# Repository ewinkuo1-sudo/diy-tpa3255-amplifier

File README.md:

# TPA3255 DIY 立體聲後級

使用 TI TPA3255 自畫電路與 PCB，搭配材料選用、3D 機構與量測，完成一台練習機／備用後級，記錄 AI 協作過程供課堂展示。

## 先看成品怎麼用

**Z10 送出音樂 → 這台後級放大 → 左右喇叭發聲。** 音量由 Z10 調整；後級機內自帶電源，機背只接一條市電電源線，另外可接 Trigger 跟隨前級開機／待機。

[白話說明與放大圖](docs/使用方式圖解.md)。這是功能與使用方式示意，外觀、內部位置及尺寸尚未定案；目前尚無實機。

## 目前進度

V0.3 已加入 **XLR 平衡輸入並保留 RCA**，搭配濾波後回授（PFFB）、四顆 Coilcraft MA5172-AE，以及隔離 Trigger、自動啟停與 48V 功率電源開關。原八頁的全部元件已按訊號路徑重新排列成 **一張連續接線的完整電路圖**，可由輸入一路看到放大、喇叭、四路回授及啟停控制；元件與電氣連接維持原版。已開始 PCB 零件配置；以 2×50W / 8Ω 為第一階段目標，尚無完成的板子或實測。

XLR 使用 INA2137 差動接收器，依 Z10 的 XLR／RCA 電平匹配音量。第一版由左右聲道跳線選擇輸入，切換前先進入待機。

整機已改為 **機內電源、機背一條市電線**：規劃單一 IEC 入口，機內分別供應 48V 主電源與 12V 待機電源。Trigger 關機只停止功率級供電，兩組 AC/DC 與 12V 支路仍有電。電源模組已有候選，交流保護、12V 入口保護、配線及熱驗證尚待完成；Z10 Trigger 的電壓、極性與帶載能力仍需實測。

## PCB 第一版配置

**[看 PCB 配置與中文說明](electrical/pcb-draft/README.md)** · [檢查結果](electrical/pcb-draft/validation.md)

已放入 180 個元件與 4 個固定孔，暫抓 22×16 公分，尺寸與料件仍需調整。**尚未走線，不能送廠製作。** 先補電源保護、定料與散熱，再細調位置和走線。

## 電路圖：輸入、放大、回授與控制接成一張大圖

**[開啟／下載單頁 PDF](electrical/v03/preview/tpa3255-v03-overview.pdf)** · [放大 SVG](electrical/v03/preview/tpa3255-v03-overview.svg) · [看圖說明](electrical/v03/README.md) · [合併檢查](electrical/v03/overview-validation.md)

總圖採 **A0 橫式單頁**，180 個元件重新編排；音訊由左往右，四路 PFFB 實際接線繞回輸入，下方整合供電與啟停控制。483 個腳位、120 個網路與原版一致，另以移除標籤的接線表確認主要路徑確實連通。PDF／SVG 可放大看數值。建議直接把單頁 PDF 傳給教授，螢幕閱讀時放大；列印以 A0 原尺寸為佳，縮到 A4 文字會太小。供電、偏壓與部分狀態線使用同名標籤相連；導線交叉處有圓點才相接。

[中文設計說明](docs/V0.3_設計說明.md) · [電路／模型驗證報告](electrical/v03/validation.md) · [原八頁 PDF](electrical/v03/preview/tpa3255-v03.pdf)

## 整機電源與機箱

[電源架構、模組候選與待辦](electrical/system-power/README.md) · [機箱製作方式](mechanical/機箱選擇.md)

採現成鋁機箱＋客製前後面板的方向，需重新容納機內電源、熱路徑與市電配線。機箱尚未定案；[原 V0.1 空間圖](mechanical/README.md) 保留為歷史占位，不代表目前整機尺寸。

## 文件

| 文件 | 用途 |
|---|---|
| [使用方式圖解](docs/使用方式圖解.md) | 先看 Z10、後級、喇叭怎麼連接，以及電源和開關怎麼用 |
| [PCB 配置草案](electrical/pcb-draft/README.md) | 真正 KiCad 板檔、180 元件初步配置、中文預覽與待辦 |
| [機內電源架構](electrical/system-power/README.md) | 單一市電入口、48V／12V 模組候選、保護接地與待機 |
| [V0.3 電路設計](docs/V0.3_設計說明.md) | 電感選型、回授、Z10 匹配與 Trigger 啟停 |
| [PCB 設計要求](docs/V0.3_PCB設計要求.md) | 供電、接地、取樣與元件配置要求 |
| [V0.2 電路設計](docs/V0.2_電路設計.md) | 歷史基線：手動控制、未加 PFFB |
| [音質改善評估](docs/V0.2_音質改善評估.md) | 回授、電感、供電與輸入級的改善優先順序 |
| [BOM 草案](electrical/v03/bom-draft.csv) | V0.3 電路元件；封裝候選另列於 PCB 草案，尚未回填定案 |
| [V0.1 設計規格](docs/V0.1_設計規格.md) | 系統、選材條件與測試流程 |
| [電路設計筆記](docs/01_電路設計.md) | 已修正的腳位、供電與設計注意事項 |
| [功率估算](docs/V0.1_功率估算.md) | 可重算的需求情境 |
| [原始規劃](docs/00_專案總覽.md) | 歷史成本與構想，待重核 |
| [接班進度](HANDOFF.md) | 下一步與驗證程度 |
| [拆分紀錄](MIGRATION.md) | 舊版本與歷史來源 |

## 下一步

補齊 12V 入口保護與交流入口／總開關選型，依機內電源的散熱需求重排機箱。同時完成回授穩定性、真實運放與電源開關的進一步驗證，核對 Trigger 介面、剩餘料件及封裝，再確定 PCB 板形、佈局和散熱器。

重新產生計算報告：

```sh
python3 tools/power_budget.py > docs/V0.1_功率估算.md
```

預覽更新方式見 [看圖說明](mechanical/README.md)。
Purifi 主力機位於 [獨立專案](https://github.com/ewinkuo1-sudo/diy-purifi-amplifier)，本專案的檔案與測試不依賴它。

## License

MIT（沿用來源專案的授權聲明）；衍生自 KiCad 的獨立封裝另依[封裝庫授權](electrical/pcb-draft/Placement.pretty/README.md)。

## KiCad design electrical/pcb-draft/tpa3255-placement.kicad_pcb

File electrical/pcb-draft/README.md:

# PCB 第一版：零件配置草案

已開始畫真正的 KiCad 電路板檔案。本階段先安排零件位置和空間，**尚未走線，不能送廠製作**。板子暫抓 220×160 mm，機箱與散熱器仍需配合調整。

[放大中文圖解](preview/placement-explained.svg) · [正面原始預覽](preview/top.png) · [背面原始預覽](preview/bottom.png) · [檢查結果](validation.md)

## 目前這張板包含什麼

- 180 個電路元件與 4 個暫定 M3 固定孔，保留原理圖接線資料。
- 左側接前級；中間放輸入處理、回授與功率晶片；右側安排四顆電感與喇叭輸出；下方安排 Trigger 與主電源開關。
- 主晶片頂部的散熱器、12V 入口保護各有空間標記。標記是配置預留，不代表完成 3D 干涉檢查或電氣隔離設計。
- 暫用 4 層、1.6 mm 板厚做空間研究；尚未核定製程、銅厚、介質、線寬、過孔或地平面，沒有畫任何銅箔走線／覆銅。
- 只包括音訊與低壓控制。兩個 AC/DC 電源、交流入口與市電線束放在機箱其他位置，不在這張板上。

分區和現有間距只是起點。高電流回路、去耦過孔、回授取樣、背面元件可裝配性及散熱器固定仍要細調；目前不能以「放得下」判定可用於實際功率輸出。

## 封裝核對與尚未定料的項目

[placement.csv](placement.csv) 每個元件一列，記錄初始封裝、正／背面、位置和來源封裝檔 SHA-256；它是生成結果，手動修改板檔後需同步更新。`package_candidate` 表示已依下列原廠資料核對封裝類型及腳序，但未完成製造放行；`provisional` 表示暫用的尺寸／封裝占位，未選定相應實際料號。

| 部分 | 本次處理與依據 |
|---|---|
| TPA3255 | 使用 DDV 44 腳頂面散熱封裝；PCB 沒有額外的第 45 腳底部散熱焊盤。依 [TI 原廠資料，封裝及 §12](https://www.ti.com/lit/ds/symlink/tpa3255.pdf)。散熱器尺寸與接觸壓力未定。 |
| 主電源開關 | TPS26631 使用 PWP0020T 對應的 HTSSOP-20 與 2.96×2.96 mm 阻焊開口版本，底部第 21 腳接 GND；散熱銅面／過孔仍未設計。[TI TPS2663](https://www.ti.com/lit/ds/symlink/tps2663.pdf) |
| XLR 接收與運放 | INA2137UA 用 SOIC-14；NE5532 暫選 SOIC-8（D 封裝方向，完整訂購料號待定）。[INA2137](https://www.ti.com/lit/ds/symlink/ina137.pdf)、[NE5532](https://www.ti.com/lit/ds/symlink/ne5532.pdf) |
| 監測／邏輯／穩壓 | TPS3808 DBV 用 6 腳 SOT-23；LVC1G14／17 DBV 用 5 腳 SOT-23；TLV760 DBZ 為 3 腳且 1=OUT、2=IN、3=GND。[TPS3808](https://www.ti.com/lit/ds/symlink/tps3808.pdf)、[LVC1G14](https://www.ti.com/lit/ds/symlink/sn74lvc1g14.pdf)、[LVC1G17](https://www.ti.com/lit/ds/symlink/sn74lvc1g17.pdf)、[TLV760](https://www.ti.com/lit/ds/symlink/tlv760.pdf) |
| Trigger 光耦 | VOS618A 用 SSOP-4，依 [Vishay 外形與腳序](https://www.vishay.com/docs/83465/vos618a.pdf)。隔離兩側仍須在走線時保持分開。 |
| 二極體 | D303 的 BAT54 由邏輯兩腳符號改成實體 1=A、2=NC、3=K，陰極接 AUX_GOOD，功能方向不變。[Nexperia BAT54](https://assets.nexperia.com/documents/data-sheet/BAT54.pdf)。D401 採 DPAK，1=A、2=K／散熱片、3=NC，[ST 資料](https://www.st.com/resource/en/datasheet/stps5h100.pdf)。D301／D302 的軸向封裝另依本專案 A=1、K=2 重新編號，陰極帶位置不變。 |
| 電感 | 自訂 MA5172-AE 占位採原廠 28.6×12.3 mm 包絡與名義 10 mm 腳距。**1.4 mm 成品孔、3 mm 焊盤是本次暫定值**，不是原廠建議；腳距 ±0.5 mm、線徑最大 1.07 mm 仍須配合孔公差、裝配及電流核定。[Coilcraft 外形圖](https://www.coilcraft.com/getmedia/5fb1a3ea-b3b6-4ae7-89c3-2a4c68c350e4/ma5172.pdf) |
| 電阻／電容／保險絲 | 封裝僅估空間。0805、1206 或 2512 尺寸不能保證耐壓、功率、電容偏壓特性或誤差；所有實際料號需補齊。無極性電容用無正負標記的專用占位；F1 與座尚未定料，圖中外形／孔距不對應已核定的產品。 |
| 插座與線束 | XLR、RCA、Trigger 和面板控制暫以板端排針占位，**不是面板插座的實際腳位／孔位**；尚需選有防呆／固定的接頭並製作線束對照。主電源與喇叭端子也只選封裝候選，額定與料號未核定。 |

## 開啟與修改

KiCad 10 開啟 [tpa3255-placement.kicad_pro](tpa3255-placement.kicad_pro)，再開同名 PCB；也可直接開 [板檔](tpa3255-placement.kicad_pcb)。原理圖維持在 [V0.3](../v03/README.md)。

本階段封裝候選由 `placement.csv`／生成器管理，**尚未回填原理圖的 Footprint 欄位**，避免把占位當成定案。正式轉入原理圖與 PCB 同步流程時，先定料、回填封裝、核對多單元符號對應，再審查「由原理圖更新 PCB」的差異。不能直接重新生成後覆蓋人工佈局。

```sh
python3 tools/verify_pcb_draft.py
python3 tools/export_pcb_draft.py
```

`tools/build_pcb_draft.py` 由最新原理圖產生初始配置，預設拒絕覆寫已有板檔；`--force` 會丟棄人工 PCB 修改。這不是佈線工具。背面預覽從背面看，左右相對正面翻轉。

PCB 草案完成後的下一步：先補 12V 保護並核定料件／散熱器，再縮短功率回路與取樣路徑、配置地平面並逐區走線。製板前仍須完整 DRC、電路與熱設計審查；試作板再量測音質、穩定度、啟停與溫升。沒有輸出 Gerber 或下單。

本機 KiCad 10.0.6 Python API 的部分舊通孔封裝寫出時會遺漏阻焊開口，生成器已補回，檢查工具會重新讀取板檔逐腳核對。這項工具相容處理不改變腳號或接線。專案自訂庫的來源與授權見 [Placement.pretty/README.md](Placement.pretty/README.md)。

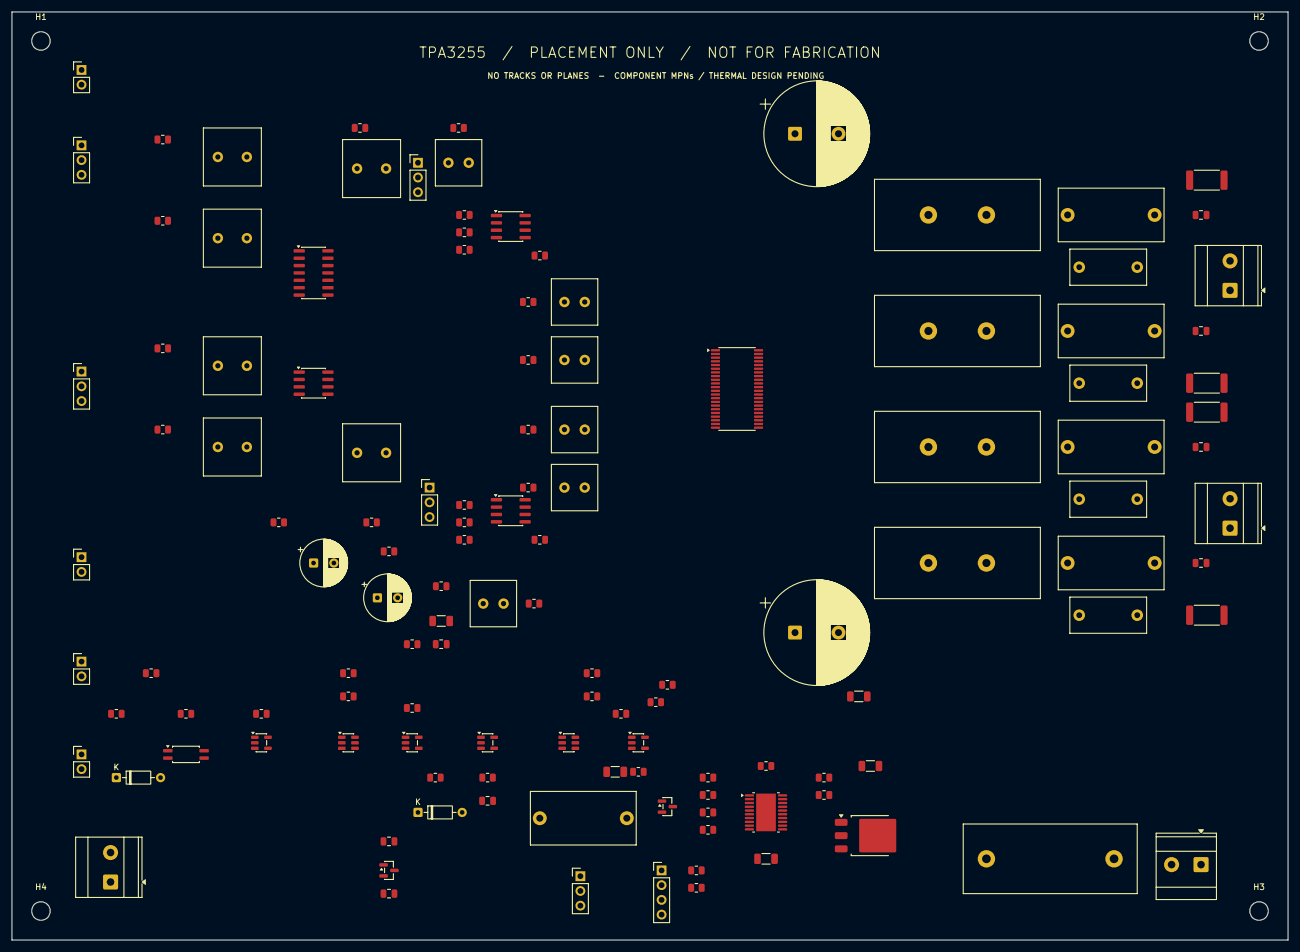
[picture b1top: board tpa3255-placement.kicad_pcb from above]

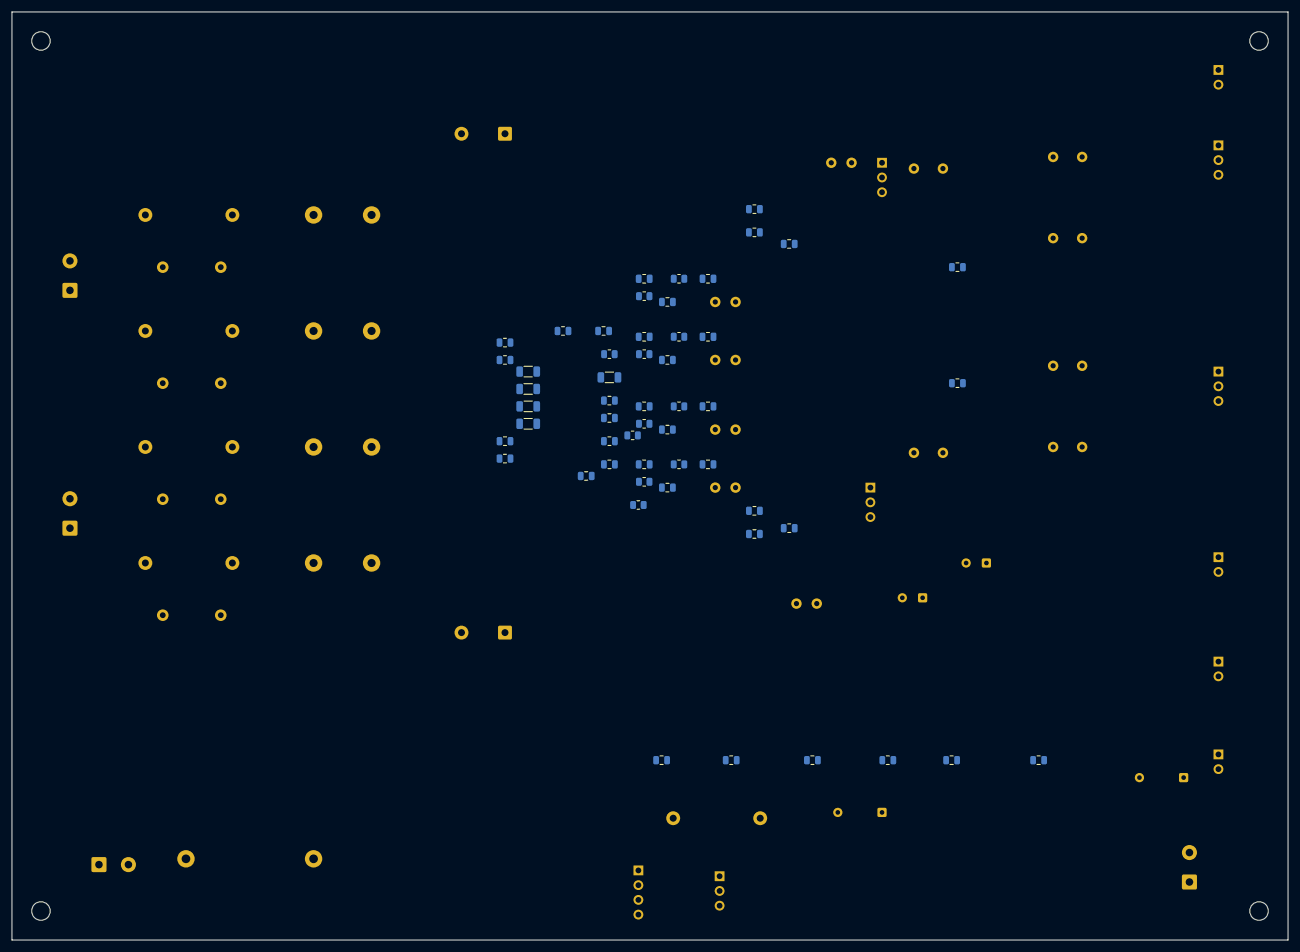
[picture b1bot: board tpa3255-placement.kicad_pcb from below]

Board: 4 copper layers, 220.0 x 160.0 mm, 184 parts (53 on the bottom side), 105 nets, no tracks yet.

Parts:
C1, C2, C3, C4: 33n / 100V; C_0805_2012Metric
C5, C6, C7, C8: 1u / 100V film; C_Rect_L18.0mm_W9.0mm_P15.00mm_FKS3_FKP3
C9, C10, C11, C12: 1n / 100V; C_0805_2012Metric
C13, C14, C15, C16: 220n / 100V film; C_Rect_L13.0mm_W6.0mm_P10.00mm_FKS3_FKP3_MKS4
C101, C121: 10u / 25V BP; BP_Cap_D8_P3.5
C102, C103, C122, C123: 330p / C0G; C_0805_2012Metric
C150, C151, C152, C153: 10u / 50V BP; BP_Cap_D8_P3.5
C154, C155, C156, C157: 100p / C0G; C_0805_2012Metric
C201, C202, C203, C204, C401: 1u / 100V X7R; C_1206_3216Metric
C205, C206: 470u / 80V; CP_Radial_D18.0mm_P7.50mm
C207: 10u / 25V; C_1206_3216Metric
C208, C209, C210, C218, C219, C607, C608: 100n / 25V; C_0805_2012Metric
C211, C212, C213, C302: 1u / 16V; C_0805_2012Metric
C214: 47n / 25V; C_0805_2012Metric
C215, C609: 100u / 25V; CP_Radial_D8.0mm_P3.50mm
C216: 10u / 16V; C_1206_3216Metric
C217, C310, C311, C312, C313, C314, C315: 100n / 16V; C_0805_2012Metric
C301: 1u / 25V; C_0805_2012Metric
C303: 1n / C0G; C_0805_2012Metric
C304: 4.7u / 16V film 5%; C_Rect_L18.0mm_W9.0mm_P15.00mm_FKS3_FKP3
C305: 180n / 5% C0G; C_1206_3216Metric
C402: 2.2u / 10V X7R; C_1206_3216Metric
C501, C502, C503, C504, C505, C506, C507, C508: 220p / 100V C0G; C_0805_2012Metric
C601, C602, C603, C604, C605, C606: 47u / 25V BP; BP_Cap_D10_P5
D301, D302: 1N4148; DO35_A1_K2_P7.62
D303: BAT54; SOT-23
D401: STPS5H100B; TO-252-3_TabPin2
F1: T5A / >=80VDC TBD MPN; Fuse_P22_Provisional
H1, H2, H3, H4: MountingHole_3.2mm_M3
J1: LEFT BTL; TerminalBlock_Phoenix_MKDS-3-2-5.08_1x02_P5.08mm_Horizontal
J2: RIGHT BTL; TerminalBlock_Phoenix_MKDS-3-2-5.08_1x02_P5.08mm_Horizontal
J101: L RCA; PinHeader_1x02_P2.54mm_Vertical
J102: R RCA; PinHeader_1x02_P2.54mm_Vertical
J201: INTERNAL 48V INPUT; TerminalBlock_Phoenix_MKDS-3-2-5.08_1x02_P5.08mm_Horizontal
J202: INTERNAL 12V INPUT; TerminalBlock_Phoenix_MKDS-3-2-5.08_1x02_P5.08mm_Horizontal
J301: TRIGGER TIP / SLEEVE; PinHeader_1x02_P2.54mm_Vertical
J302: AUTO / COMMON / ON; PinHeader_1x03_P2.54mm_Vertical
J303: STATUS; PinHeader_1x04_P2.54mm_Vertical
J601: L XLR FEMALE; PinHeader_1x03_P2.54mm_Vertical
J602: R XLR FEMALE; PinHeader_1x03_P2.54mm_Vertical
J603: L RCA / COM / XLR; PinHeader_1x03_P2.54mm_Vertical
J604: R RCA / COM / XLR; PinHeader_1x03_P2.54mm_Vertical
J605: CHASSIS BOND; PinHeader_1x02_P2.54mm_Vertical
L1, L2, L3, L4: 10u / MA5172-AE; MA5172_AE_Provisional
R1, R2, R3, R4: 1 / 1W; R_2512_6332Metric
R101, R121, R305, R605, R606: 100k; R_0805_2012Metric
R102, R122: 11.5k / 0.1%; R_0805_2012Metric
R103, R104, R105, R123, R124, R125, R307, R312, R402, R404, R406, R505, R506, R507, R508: 10k / 0.1%; R_0805_2012Metric
R150, R151, R152, R153: 2.7k / 0.1%; R_0805_2012Metric
R201: 3.3; R_0805_2012Metric
R202, R304: 22k / 1%; R_0805_2012Metric
R203: 30k / 1%; R_0805_2012Metric
R204, R607: 10; R_0805_2012Metric
R205, R206: 10k / 1%; R_0805_2012Metric
R301: 1k / 1%; R_0805_2012Metric
R302: 4.7k / 1%; R_0805_2012Metric
R303: 6.8k / 1%; R_0805_2012Metric
R306: 267k / 0.1%; R_0805_2012Metric
R308, R313, R314: 10k; R_0805_2012Metric
R309, R408: 1k; R_0805_2012Metric
R310: 100k / 1%; R_0805_2012Metric
R311: 1M / 0.1%; R_0805_2012Metric
R401: 324k / 0.1%; R_0805_2012Metric
R403: 412k / 0.1%; R_0805_2012Metric
R405: 316k / 0.1%; R_0805_2012Metric
R407: 4.02k / 1%; R_0805_2012Metric
R409: 22k; R_0805_2012Metric
R410: 22k / 0.5W; R_1206_3216Metric
R501, R502, R503, R504: 33k / 0.1%; R_0805_2012Metric
R601, R602, R603, R604: 47 / 0.1%; R_0805_2012Metric
R608: 0 / SINGLE BOND; R_0805_2012Metric
U1: TPA3255DDV; HTSSOP-44_6.1x14mm_P0.635mm_TopEP4.14x7.01mm
U2, U3, U602: NE5532; SOIC-8_3.9x4.9mm_P1.27mm
U4: TLV76033DBZR; SOT-23
U301: VOS618A-3T; SSOP-4_4.4x2.6mm_P1.27mm
U302: SN74LVC1G14DBVR; SOT-23-5
U303, U306: TPS3808G01DBVR; SOT-23-6
U304, U305, U307: SN74LVC1G17DBVR; SOT-23-5
U401: TPS26631PWPR; HTSSOP-20-1EP_4.4x6.5mm_P0.65mm_EP3.4x6.5mm_Mask2.96x2.96mm
U601: INA2137UA; SOIC-14_3.9x8.7mm_P1.27mm

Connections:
+3V3_CTRL: C302.1, C310.1, C311.1, C312.1, C313.1, C314.1, C315.1, J302.3, R304.1, R308.1, R313.1, R314.1, U4.1 (OUT), U302.5 (VCC), U303.6 (VDD), U304.5 (VCC), U305.5 (VCC), U306.6 (VDD), U307.5 (VCC)
+12V: C209.1, C210.1, C301.1, J202.1, R201.1, R204.1, R306.1, R607.1, U1.1 (GVDD_AB), U1.22 (GVDD_CD), U4.2 (IN)
+12V_AUDIO: C215.1, C218.1, C219.1, R204.2, R205.1, U2.8 (V+), U3.8 (V+)
+12V_XLR: C607.1, C608.1, C609.1, R607.2, U601.11 (V+), U602.8 (V+)
AUDIO_DELAY: C305.1, U306.4 (CT)
AUDIO_GOOD: R314.2, U306.1 (RESET_N), U307.2 (A)
AUDIO_MR: D303.1 (A), R313.2, U306.3 (MR_N), U401.17 (PGOOD)
AUTO_REQUEST: J302.1, U302.4 (Y)
AUX_BUFFER: R309.1, U304.4 (Y)
AUX_GOOD: D303.3 (K), R308.2, U303.1 (RESET_N), U304.2 (A)
AVDD: C212.1, U1.14 (AVDD)
BST_A: C1.1, U1.44 (BST_A)
BST_B: C2.1, U1.43 (BST_B)
BST_C: C3.1, U1.24 (BST_C)
BST_D: C4.1, U1.23 (BST_D)
CHASSIS: J601.1, J602.1, J605.1, J605.2, R608.1
CLIP_OTW_N: J303.3, U1.21 (CLIP_OTW_N)
C_START: C214.1, U1.15 (C_START)
DC_PROTECTED: C401.1, D401.2 (K_TAB), R401.1, R403.1, U401.1 (IN), U401.2 (IN), U401.3 (IN), U401.6 (IN_SYS)
DVDD: C211.1, U1.11 (DVDD)
EFUSE_DVDT: C402.1, U401.10 (dVdT)
EFUSE_ENABLE: R408.1, U305.4 (Y)
EFUSE_FAULT_N: J303.4, U401.15 (FLT_N)
EFUSE_ILIM: R407.1, U401.11 (ILIM)
EFUSE_OV: R403.2, R404.1, U401.8 (OVP)
EFUSE_PGTH: R405.2, R406.1, U401.16 (PGTH)
EFUSE_SHDN: R408.2, R409.1, U401.13 (SHDN)
EFUSE_UV: R401.2, R402.1, U401.7 (UVLO)
FAULT_N: J303.2, U1.19 (FAULT_N)
FB_MID_A: C501.2, C505.1, R505.1
FB_MID_B: C502.2, C506.1, R506.1
FB_MID_C: C503.2, C507.1, R507.1
FB_MID_D: C504.2, C508.1, R508.1
FREQ_ADJ: R203.1, U1.8 (FREQ_ADJ)
FUSED_48V: D401.1 (A), F1.2
GND: C5.2, C6.2, C7.2, C8.2, C9.2, C10.2, C11.2, C12.2, C154.2, C155.2, C156.2, C157.2, C201.2, C202.2, C203.2, C204.2, C205.2, C206.2, C207.2, C208.2, C209.2, C210.2, C211.2, C212.2, C213.2, C214.2, C215.2, C216.2, C217.2, C218.2, C219.2, C301.2, C302.2, C303.2, C304.2, C305.2, C310.2, C311.2, C312.2, C313.2, C314.2, C315.2, C401.2, C402.2, C607.2, C608.2, C609.2, J101.2, J102.2, J201.2, J202.2, J303.1, R1.2, R2.2, R3.2, R4.2, R101.2, R121.2, R202.2, R203.2, R206.2, R302.2, R305.2, R307.2, R310.2, R312.2, R402.2, R404.2, R406.2, R407.2, R409.2, R410.2, R505.2, R506.2, R507.2, R508.2, R605.2, R606.2, R608.2, U1.3 (M1), U1.4 (M2), U1.12 (GND), U1.13 (GND), U1.25 (GND), U1.26 (GND), U1.33 (GND), U1.34 (GND), U1.41 (GND), U1.42 (GND), U2.4 (V-), U3.4 (V-), U4.3 (GND), U301.3 (E), U302.3 (GND), U303.2 (GND), U304.3 (GND), U305.3 (GND), U306.2 (GND), U307.3 (GND), U401.9 (GND), U401.21 (PAD), U601.4 (V-), U602.4 (V-)
HOLD_CAP: C304.1, D302.2 (K), R310.1, U305.2 (A)
HOLD_CHARGE: D302.1 (A), R309.2
INPUT_A: C150.2, C154.1, U1.5 (INPUT_A)
INPUT_B: C151.2, C155.1, U1.6 (INPUT_B)
INPUT_C: C152.2, C156.1, U1.16 (INPUT_C)
INPUT_D: C153.2, C157.1, U1.17 (INPUT_D)
L_LINE_COLD: C602.1, R602.2
L_LINE_HOT: C601.1, R601.2
L_NEG: C102.2, R103.2, R104.1, R150.1, U2.1 (OUT)
L_POS: C103.2, R105.2, R151.1, U2.7 (OUT)
L_RCA: J101.1, J603.1, R101.1
L_RX_COLD: C602.2, U601.2 (IN_A-)
L_RX_HOT: C601.2, U601.3 (IN_A+)
L_RX_OUT: C605.1, U601.12 (SENSE_A), U601.13 (OUT_A)
L_RX_REF: U601.14 (REF_A), U602.1 (OUT), U602.2 (-)
L_SELECTED: C101.1, J603.2
L_XLR: C605.2, J603.3, R605.1
L_XLR_COLD: J601.3, R602.1
L_XLR_HOT: J601.2, R601.1
unnamed: C101.2, R102.1
unnamed: C121.2, R122.1
unnamed: C102.1, R102.2, R103.1, U2.2 (-)
unnamed: C103.1, R104.2, R105.1, U2.6 (-)
unnamed: C122.1, R122.2, R123.1, U3.2 (-)
unnamed: C123.1, R124.2, R125.1, U3.6 (-)
OC_ADJ: R202.1, U1.7 (OC_ADJ)
OUT_A: C1.2, L1.1, U1.39 (OUT_A), U1.40 (OUT_A)
OUT_B: C2.2, L2.1, U1.35 (OUT_B)
OUT_C: C3.2, L3.1, U1.32 (OUT_C)
OUT_D: C4.2, L4.1, U1.27 (OUT_D), U1.28 (OUT_D)
PVDD: C201.1, C202.1, C203.1, C204.1, C205.1, C206.1, R311.1, R405.1, R410.1, U1.29 (PVDD_CD), U1.30 (PVDD_CD), U1.31 (PVDD_CD), U1.36 (PVDD_AB), U1.37 (PVDD_AB), U1.38 (PVDD_AB), U401.18 (OUT), U401.19 (OUT), U401.20 (OUT)
PVDD_IN: F1.1, J201.1
RESET_DRIVE: R301.1, U307.4 (Y)
RESET_N: R301.2, R302.1, U1.18 (RESET_N)
RUN_REQUEST: J302.2, R305.1, U303.3 (MR_N)
R_LINE_COLD: C604.1, R604.2
R_LINE_HOT: C603.1, R603.2
R_NEG: C122.2, R123.2, R124.1, R152.1, U3.1 (OUT)
R_POS: C123.2, R125.2, R153.1, U3.7 (OUT)
R_RCA: J102.1, J604.1, R121.1
R_RX_COLD: C604.2, U601.6 (IN_B-)
R_RX_HOT: C603.2, U601.5 (IN_B+)
R_RX_OUT: C606.1, U601.9 (OUT_B), U601.10 (SENSE_B)
R_RX_REF: U601.8 (REF_B), U602.6 (-), U602.7 (OUT)
R_SELECTED: C121.1, J604.2
R_XLR: C606.2, J604.3, R606.1
R_XLR_COLD: J602.3, R604.1
R_XLR_HOT: J602.2, R603.1
SENSE_12V: C303.1, R306.2, R307.1, U303.5 (SENSE)
SENSE_PVDD: R311.2, R312.1, U306.5 (SENSE)
SPK_A: C5.1, C9.1, C13.1, C505.2, J1.1, L1.2, R501.2
SPK_B: C6.1, C10.1, C14.1, C506.2, J1.2, L2.2, R502.2
SPK_C: C7.1, C11.1, C15.1, C507.2, J2.1, L3.2, R503.2
SPK_D: C8.1, C12.1, C16.1, C508.2, J2.2, L4.2, R504.2
SUM_A: C150.1, C501.1, R150.2, R501.1
SUM_B: C151.1, C502.1, R151.2, R502.1
SUM_C: C152.1, C503.1, R152.2, R503.1
SUM_D: C153.1, C504.1, R153.2, R504.1
TRIG_LED: D301.2 (K), R303.2, U301.1 (A)
TRIG_N: R304.2, U301.4 (C), U302.2 (A)
TRIG_RETURN: D301.1 (A), J301.2, U301.2 (K)
TRIG_TIP: J301.1, R303.1
VBG: C213.1, U1.20 (VBG)
VDD_FILTERED: C207.1, C208.1, R201.2, U1.2 (VDD)
VMID: C216.1, C217.1, R205.2, R206.1, U2.3 (+), U2.5 (+), U3.3 (+), U3.5 (+), U602.3 (+), U602.5 (+)
Z_A: C13.2, R1.1
Z_B: C14.2, R2.1
Z_C: C15.2, R3.1
Z_D: C16.2, R4.1

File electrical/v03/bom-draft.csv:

"Refs","Value","Footprint","Qty","DNP"
"C1-C4","33n / 100V","","4",""
"C5-C8","1u / 100V film","","4",""
"C9-C12","1n / 100V","","4",""
"C13-C16","220n / 100V film","","4",""
"C101,C121","10u / 25V BP","","2",""
"C102,C103,C122,C123","330p / C0G","","4",""
"C150-C153","10u / 50V BP","","4",""
"C154-C157","100p / C0G","","4",""
"C201-C204,C401","1u / 100V X7R","","5",""
"C205,C206","470u / 80V","","2",""
"C207","10u / 25V","","1",""
"C208-C210,C218,C219,C607,C608","100n / 25V","","7",""
"C211-C213,C302","1u / 16V","","4",""
"C214","47n / 25V","","1",""
"C215,C609","100u / 25V","","2",""
"C216","10u / 16V","","1",""
"C217,C310-C315","100n / 16V","","7",""
"C301","1u / 25V","","1",""
"C303","1n / C0G","","1",""
"C304","4.7u / 16V film 5%","","1",""
"C305","180n / 5% C0G","","1",""
"C402","2.2u / 10V X7R","","1",""
"C501-C508","220p / 100V C0G","","8",""
"C601-C606","47u / 25V BP","","6",""
"D301,D302","1N4148","","2",""
"D303","BAT54","","1",""
"D401","STPS5H100B","","1",""
"F1","T5A / >=80VDC TBD MPN","","1",""
"J1","LEFT BTL","","1",""
"J2","RIGHT BTL","","1",""
"J101","L RCA","","1",""
"J102","R RCA","","1",""
"J201","INTERNAL 48V INPUT","","1",""
"J202","INTERNAL 12V INPUT","","1",""
"J301","TRIGGER TIP / SLEEVE","","1",""
"J302","AUTO / COMMON / ON","","1",""
"J303","STATUS","","1",""
"J601","L XLR FEMALE","","1",""
"J602","R XLR FEMALE","","1",""
"J603","L RCA / COM / XLR","","1",""
"J604","R RCA / COM / XLR","","1",""
"J605","CHASSIS BOND","","1",""
"L1-L4","10u / MA5172-AE","","4",""
"R1-R4","1 / 1W","","4",""
"R101,R121,R305,R605,R606","100k","","5",""
"R102,R122","11.5k / 0.1%","","2",""
"R103-R105,R123-R125,R307,R312,R402,R404,R406,R505-R508","10k / 0.1%","","15",""
"R150-R153","2.7k / 0.1%","","4",""
"R201","3.3","","1",""
"R202,R304","22k / 1%","","2",""
"R203","30k / 1%","","1",""
"R204,R607","10","","2",""
"R205,R206","10k / 1%","","2",""
"R301","1k / 1%","","1",""
"R302","4.7k / 1%","","1",""
"R303","6.8k / 1%","","1",""
"R306","267k / 0.1%","","1",""
"R308,R313,R314","10k","","3",""
"R309,R408","1k","","2",""
"R310","100k / 1%","","1",""
"R311","1M / 0.1%","","1",""
"R401","324k / 0.1%","","1",""
"R403","412k / 0.1%","","1",""
"R405","316k / 0.1%","","1",""
"R407","4.02k / 1%","","1",""
"R409","22k","","1",""
"R410","22k / 0.5W","","1",""
"R501-R504","33k / 0.1%","","4",""
"R601-R604","47 / 0.1%","","4",""
"R608","0 / SINGLE BOND","","1",""
"U1","TPA3255DDV","","1",""
"U2,U3,U602","NE5532","","3",""
"U4","TLV76033DBZR","","1",""
"U301","VOS618A-3T","","1",""
"U302","SN74LVC1G14DBVR","","1",""
"U303,U306","TPS3808G01DBVR","","2",""
"U304,U305,U307","SN74LVC1G17DBVR","","3",""
"U401","TPS26631PWPR","","1",""
"U601","INA2137UA","","1",""

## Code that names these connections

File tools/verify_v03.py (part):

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        def pins(ref,mapping):
            for pin,name in mapping.items(): assert net(ref,pin)==name,(ref,pin,name)
        # Critical checks use physical pin numbers independently of the drawing generator.
        pins('U1',{1:'+12V',2:'VDD_FILTERED',3:'GND',4:'GND',5:'INPUT_A',6:'INPUT_B',
                   11:'DVDD',14:'AVDD',16:'INPUT_C',17:'INPUT_D',18:'RESET_N',20:'VBG',22:'+12V'})
        for n in [29,30,31,36,37,38]:pins('U1',{n:'PVDD'})
        for n in [12,13,25,26,33,34,41,42]:pins('U1',{n:'GND'})
        pins('U1',{39:'OUT_A',40:'OUT_A',27:'OUT_D',28:'OUT_D'})
        for i,(bst,out) in enumerate([(44,40),(43,35),(24,32),(23,28)],1):
            assert net('C'+str(i),1)==net('U1',bst)
            assert net('C'+str(i),2)==net('U1',out)
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            pins('C'+str(505+i),{1:'FB_MID_'+ch,2:'SPK_'+ch})
            pins('R'+str(505+i),{1:'FB_MID_'+ch,2:'GND'})
        assert groups['TRIG_RETURN']=={('J301','2'),('D301','1'),('U301','2')}
        pins('U301',{1:'TRIG_LED',2:'TRIG_RETURN',3:'GND',4:'TRIG_N'})
        pins('D301',{1:'TRIG_RETURN',2:'TRIG_LED'})
        pins('U303',{1:'AUX_GOOD',2:'GND',3:'RUN_REQUEST',5:'SENSE_12V',6:'+3V3_CTRL'})
        pins('D302',{1:'HOLD_CHARGE',2:'HOLD_CAP'})
        # BAT54 SOT-23: physical pin 2 is NC; cathode is pin 3.
        pins('D303',{1:'AUDIO_MR',3:'AUX_GOOD'})
        assert len(groups[net('D303',2)])==1
        pins('U306',{1:'AUDIO_GOOD',2:'GND',3:'AUDIO_MR',4:'AUDIO_DELAY',5:'SENSE_PVDD',6:'+3V3_CTRL'})
        pins('U401',{1:'DC_PROTECTED',2:'DC_PROTECTED',3:'DC_PROTECTED',6:'DC_PROTECTED',
                     7:'EFUSE_UV',8:'EFUSE_OV',9:'GND',10:'EFUSE_DVDT',11:'EFUSE_ILIM',
                     13:'EFUSE_SHDN',16:'EFUSE_PGTH',17:'AUDIO_MR',18:'PVDD',19:'PVDD',20:'PVDD',21:'GND'})
        pins('D401',{1:'FUSED_48V',2:'DC_PROTECTED'})
        pins('U601',{2:'L_RX_COLD',3:'L_RX_HOT',4:'GND',5:'R_RX_HOT',6:'R_RX_COLD',
                     8:'R_RX_REF',9:'R_RX_OUT',10:'R_RX_OUT',11:'+12V_XLR',12:'L_RX_OUT',13:'L_RX_OUT',14:'L_RX_REF'})
        pins('U602',{1:'L_RX_REF',2:'L_RX_REF',3:'VMID',4:'GND',5:'VMID',6:'R_RX_REF',7:'R_RX_REF',8:'+12V_XLR'})
        for idx,ch in enumerate(('L','R')):
            pins('J'+str(601+idx),{1:'CHASSIS',2:ch+'_XLR_HOT',3:ch+'_XLR_COLD'})
            pins('J'+str(603+idx),{1:ch+'_RCA',2:ch+'_SELECTED',3:ch+'_XLR'})
            pins('C'+str(101+20*idx),{1:ch+'_SELECTED'})
            assert net('C'+str(101+20*idx),2)==net('R'+str(102+20*idx),1)
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                pins('C'+str(601+2*idx+offset),{1:ch+'_LINE_'+leg,2:ch+'_RX_'+leg})
            pins('C'+str(605+idx),{1:ch+'_RX_OUT',2:ch+'_XLR'})
        assert groups['CHASSIS']=={('J601','1'),('J602','1'),('J605','1'),('J605','2'),('R608','1')}
        pins('R608',{1:'CHASSIS',2:'GND'})
        for ref in ['U302','U304','U305','U307']:pins(ref,{3:'GND',5:'+3V3_CTRL'})
        pins('U302',{2:'TRIG_N',4:'AUTO_REQUEST'})
        pins('U304',{2:'AUX_GOOD',4:'AUX_BUFFER'})
        pins('U305',{2:'HOLD_CAP',4:'EFUSE_ENABLE'})
        pins('U307',{2:'AUDIO_GOOD',4:'RESET_DRIVE'})
        for ref,ps in [('U401',[4,5,12,14]),('U303',[4])]:
            for pin in ps: assert len(groups[net(ref,pin)])==1

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        for mode,load,pole,mismatch in cases:
            case=f'ac-{mode}-{int(load) if load<1e8 else "open"}-pole{pole}'+('-mismatch' if mismatch else '')
            lines=['V0.3 REDUCED AC model - not TPA3255 PWM or hardware stability proof',
                   '* Ideal opamps (A0=1e6), ideal VMID; no noise, clipping or real opamp BW.',
                   '* INA2137: nominal internal 12k/6k network, not manufacturer semiconductor model.',
                   '* Common-mode mismatch: external R +/-0.1%, paired C +/-0.5%; internal ratios ideal.',
                   '* TPA gain is a typical constant; 100kHz pole case is an arbitrary sensitivity study.',
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
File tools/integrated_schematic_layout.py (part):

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    d.shunt('C215',45,192,(45,184)); d.place('R205',65,190,270); d.shunt('R206',65,202)
    d.wire('+12V_AUDIO',('R204',2),(171,184))
    d.wire('+12V_AUDIO',(65,184),('R205',1))
    d.join(('R205',2),('R206',1)); d.label('VMID',(65,196))
    for ref,x in [('C216',80),('C217',96)]: d.shunt(ref,x,202,(x,196))
    d.wire('VMID',(65,196),(96,196))
    for ref,x,c in [('U2',135,'C218'),('U3',160,'C219')]:
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    for ref,x in zip(['C201','C202','C203','C204','C205','C206'],[344,361,378,395,417,439]): d.shunt(ref,x,110,(x,99))
    d.wire('PVDD',(334,99),(456,99),(456,267))
    for pin,y in [(38,69),(37,71),(36,73),(31,103),(30,105),(29,107)]:
        d.wire('PVDD',('U1',pin),(334,y),(334,99))
    d.place('U4',30,235); d.shunt('C301',16,243,(16,235)); d.shunt('C302',46,243,(46,235))
    d.wire('+12V',(25,214),(10,214),(10,235),(16,235),('U4',2))
    d.wire('+3V3_CTRL',('U4',1),(46,235)); d.stub('U4',3,2)
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    d.join(('J201',1),('F1',1)); d.join(('F1',2),('D401',1))
    d.shunt('C401',291,285,(291,276)); d.place('#FLG6',289,276)
    d.wire('DC_PROTECTED',('D401',2),(306,276),(306,267),('U401',1))
    for pin,y in [(2,269),(3,271),(6,273)]: d.wire('DC_PROTECTED',('U401',pin),(306,y))
    d.wire('PVDD',('U401',20),(456,267))
    for pin,y in [(19,269),(18,271)]: d.wire('PVDD',('U401',pin),(331,y),(331,267))
    d.shunt('R410',444,274,(444,267))
    # Local protection thresholds and timing components.
    for top,bottom,x,y,net,pin,rail in [('R401','R402',266,303,'EFUSE_UV',7,'DC_PROTECTED'),('R403','R404',287,303,'EFUSE_OV',8,'DC_PROTECTED'),('R405','R406',342,282,'EFUSE_PGTH',16,'PVDD')]:
        d.place(top,x,y-6,270); d.shunt(bottom,x,y+6)
        d.join((top,2),(bottom,1)); d.label(net,(x,y))
        if pin==16: d.wire(net,('U401',pin),(335,275),(335,y),(x,y))
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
